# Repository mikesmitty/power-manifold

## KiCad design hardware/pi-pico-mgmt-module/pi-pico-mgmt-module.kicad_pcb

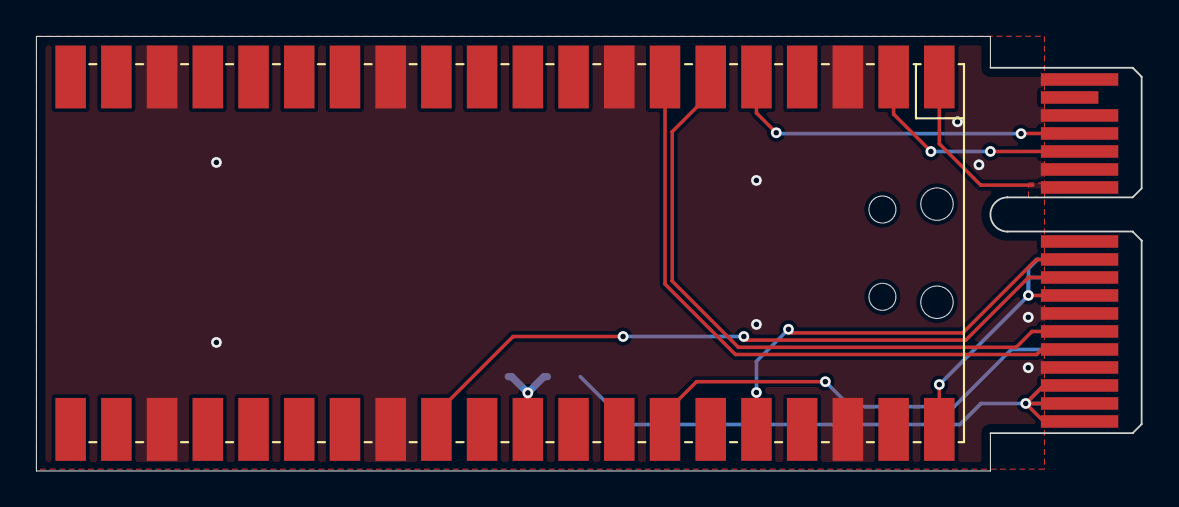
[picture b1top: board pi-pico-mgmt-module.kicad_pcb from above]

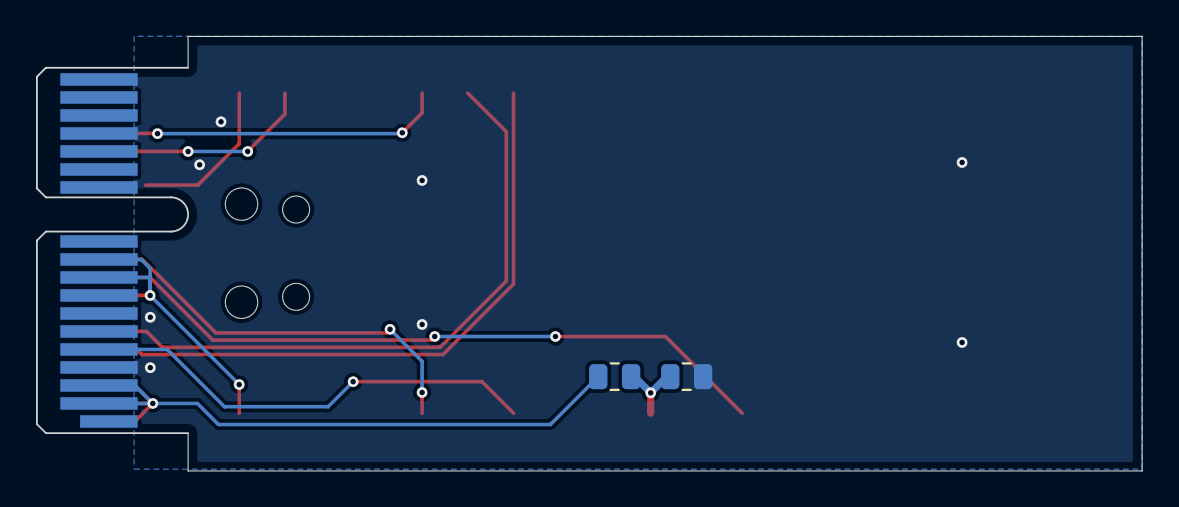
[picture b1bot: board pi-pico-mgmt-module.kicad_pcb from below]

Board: 2 copper layers, 61.4 x 24.1 mm, 4 parts (2 on the bottom side), 12 nets.

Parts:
J1: Bus_PCI_Express_x1; BUS_PCIexpress_x1
R1: 22K; R_0805_2012Metric
R2: 2K; R_0805_2012Metric
U1: W5500-EVB-Pico; RPi_Pico_W5500_SMD_NO_HOLES

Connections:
+5V: J1.A9 (+3.3V), J1.A10 (+3.3V), J1.B8 (+3.3V), U1.40 (VBUS)
GND: J1.A4 (GND), J1.A12 (GND), J1.A15 (GND), J1.A18 (GND), J1.B4 (GND), J1.B7 (GND), J1.B13 (GND), J1.B16 (GND), J1.B18 (GND), R2.2, U1.3 (GND), U1.8 (GND), U1.13 (GND), U1.18 (GND), U1.23 (GND), U1.28 (GND), U1.38 (GND)
I2C_A0: J1.B5 (SMCLK), U1.7 (GPIO5)
I2C_A1: J1.B6 (SMDAT), U1.6 (GPIO4)
I2C_A2: J1.B15 (PETn0), U1.5 (GPIO3)
I2C_RESET: J1.B9 (JTAG1), U1.29 (GPIO22)
unnamed: R1.2, R2.1, U1.31 (GPIO26_ADC0)
OVERLOAD: J1.A5 (JTAG2), U1.34 (GPIO28_ADC2)
SCL: J1.B14 (PETp0), U1.2 (GPIO1)
SDA: J1.B12 (RSVD), U1.1 (GPIO0)
VDD: J1.B10 (3.3Vaux), U1.36 (3V3)
VIN: J1.A2 (+12V), J1.A3 (+12V), J1.B1 (+12V), J1.B2 (+12V), J1.B3 (+12V), R1.1

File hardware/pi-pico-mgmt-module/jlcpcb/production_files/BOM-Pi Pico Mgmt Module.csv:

Comment,Designator,Footprint,LCSC
22K,R1,R_0805_2012Metric,C17560
2K,R2,R_0805_2012Metric,C17604

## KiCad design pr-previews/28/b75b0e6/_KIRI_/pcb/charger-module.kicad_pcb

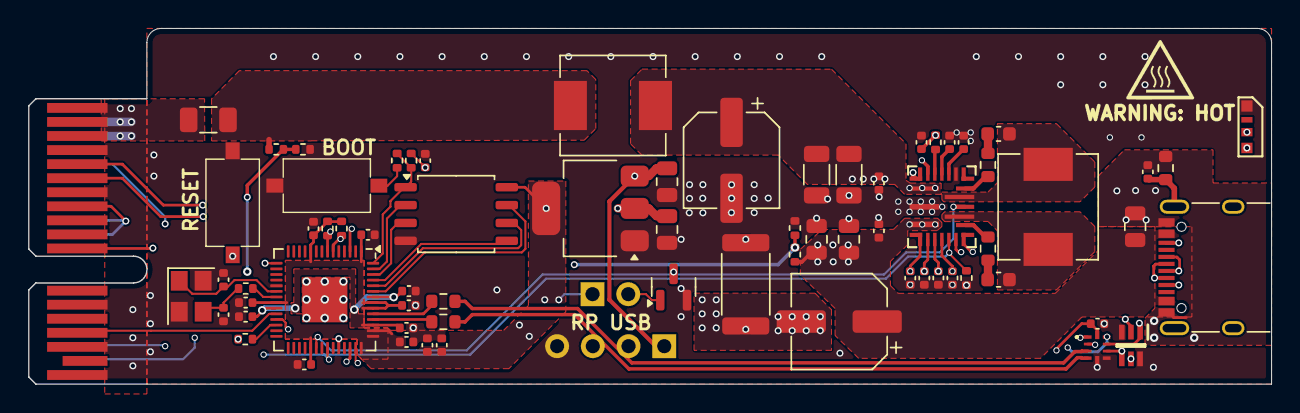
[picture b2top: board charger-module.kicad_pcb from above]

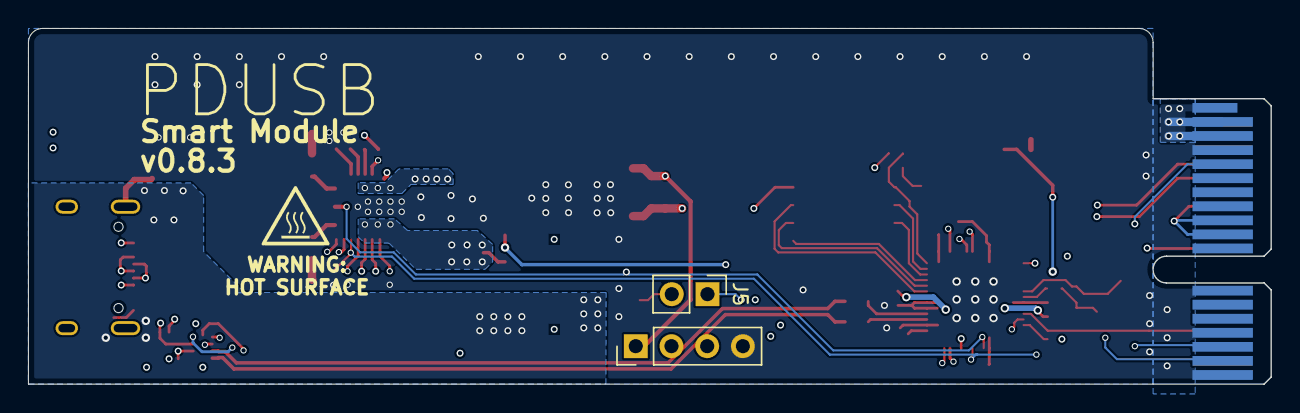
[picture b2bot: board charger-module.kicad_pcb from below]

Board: 4 copper layers, 88.4 x 25.3 mm, 72 parts (2 on the bottom side), 53 nets.

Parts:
C1, C4, C21, C24, C28: 10uF; C_0805_2012Metric
C2, C3: 39pF; C_0402_1005Metric
C5, C6, C9, C14, C15, C17, C20, C22, C25, C26, C27, C30, C35: 100nF; C_0402_1005Metric
C7, C10, C16: 2.2uF; C_0402_1005Metric
C8, C31, C32, C33, C34, C36: 470pF; C_0402_1005Metric
C11, C29: 100uF; CP_Elec_6.3x7.7
C12, C13: 4.7uF; C_1206_3216Metric
C18, C23: 220nF; C_0603_1608Metric
C19: 4.7nF; C_0402_1005Metric
D1: SZESD1L001W1T2G; SOT65P210X110-6N
D2: STATUS_LED; LED_Neopixel_Side_Light_SK6812
F1: 5A; Fuse_1206_3216Metric
J2: Bus_PCI_Express_x1; BUS_PCIexpress_x1
J3: RP_USB; PinHeader_1x04_P2.54mm_Vertical
J4: USB_C_Receptacle_USB2.0_14P; USB_C_Receptacle_XKB_U262-16XN-4BVC11
J5: USB_SW; PinHeader_1x02_P2.54mm_Vertical
L1, L2: 4.7uH; L_Sunlord_MWSA0603S
Q1: 2N7002; SOT-23
R1, R3, R4: 1K; R_0402_1005Metric
R2, R5, R11, R13: 10K; R_0402_1005Metric
R6: R010; R_2512_6332Metric
R7: 10R; R_0603_1608Metric
R8: 4.7K; R_0402_1005Metric
R9, R10: 27R; R_0603_1608Metric
R12: 0R; R_0603_1608Metric
R14, R16: 22K; R_0402_1005Metric
R15: 2K; R_0402_1005Metric
R17: 3.3K; R_0402_1005Metric
R18: 100K; R_0603_1608Metric
SW1, SW2: RESET; XKB_TS-1101_SWITCH
U1: AMS1117-3.3; SOT-223-3_TabPin2
U2: W25Q32JVSSIQ; SOIC-8_5.23x5.23mm_P1.27mm
U3: RP2040; QFN-56-1EP_7x7mm_P0.4mm_EP3.2x3.2mm
U4: MPQ4242; MPQ4242_QNF-22_4mmx5mm
U5: TS3USB3000RSER
Y1: X322512MSB4SI; Crystal_SMD_3225-4Pin_3.2x2.5mm

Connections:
+1V1: C6.1, C9.1, C10.1, U3.23 (DVDD), U3.45 (VREG_VOUT), U3.50 (DVDD)
+3.3V: C4.1, C5.1, C15.1, C16.1, C17.1, C20.1, C22.1, C25.1, C27.1, C30.1, C36.1, J5.1, R2.1, R11.1, R13.1, U1.2 (VO), U2.8 (VCC), U3.1 (IOVDD), U3.10 (IOVDD), U3.22 (IOVDD), U3.33 (IOVDD), U3.42 (IOVDD), U3.43 (ADC_AVDD), U3.44 (VREG_IN), U3.48 (USB_VDD), U3.49 (IOVDD), U5.10 (VCC)
+5V: C1.1, D2.2 (VDD), J2.A9 (+3.3V), J2.A10 (+3.3V), J2.B8 (+3.3V), J3.1, U1.3 (VI)
/EMI_VIN: C11.1, C12.1, C13.1, C14.1, L1.2, U4.1 (VIN)
/INDUCTOR: C18.2, L2.1, U4.14 (SW1)
/OUTDUCTOR: C23.1, L2.2, U4.12 (SW2)
/QSPI_SCLK: U2.6 (CLK), U3.52 (QSPI_SCLK)
/QSPI_SD0: U2.5 (DI(IO0)), U3.53 (QSPI_SD0)
/QSPI_SD1: U2.2 (DO(IO1)), U3.55 (QSPI_SD1)
/QSPI_SD2: U2.3 (IO2), U3.54 (QSPI_SD2)
/QSPI_SD3: U2.7 (IO3), U3.51 (QSPI_SD3)
/QSPI_SS: R1.1, R2.2, U2.1 (~CS), U3.56 (QSPI_SS)
/RUN: R4.2, U3.26 (RUN)
/SWCLK: J2.B15 (PETn0), U3.24 (SWCLK)
/SWD: J2.A5 (JTAG2), U3.25 (SWD)
/VIN_PREFUSE: F1.2, J2.A1 (~PRSNT1), J2.A2 (+12V), J2.A3 (+12V), J2.B1 (+12V), J2.B2 (+12V), J2.B3 (+12V)
/XIN: C2.1, U3.20 (XIN), Y1.1
/XOUT: R3.1, U3.21 (XOUT)
ALERT: J2.A17 (PERn0), U3.15 (GPIO12)
CC1: C33.1, D1.2 (C2), J4.A5 (CC1), U4.7 (CC1)
CC2: C34.1, D1.5 (C4), J4.B5 (CC2), U4.4 (CC2)
D+: D1.1 (C1), J4.A6 (D+), J4.B6 (D+), U5.8 (D+)
D-: D1.4 (C3), J4.A7 (D-), J4.B7 (D-), U5.7 (D-)
ENABLE: Q1.3 (D), U3.34 (GPIO22), U4.13 (EN)
GND: C1.2, C2.2, C3.2, C4.2, C5.2, C6.2, C7.2, C8.2, C9.2, C10.2, C11.2, C12.2, C13.2, C14.2, C15.2, C16.2, C17.2, C19.1, C20.2, C21.2, C22.2, C24.2, C25.2, C26.2, C27.2, C30.2, C31.2, C32.2, C33.2, C34.2, C36.2, D1.3 (A/3+4), D1.6 (A/1+2), D2.4 (GND), J2.A4 (GND), J2.A12 (GND), J2.A15 (GND), J2.A18 (GND), J2.B4 (GND), J2.B7 (GND), J2.B13 (GND), J2.B16 (GND), J2.B18 (GND), J3.4, Q1.2 (S), R5.2, R6.1, R15.2, R17.2, SW1.1, SW2.1, U1.1 (GND), U2.4 (GND), U3.19 (TESTEN), U3.57 (GND), U4.2 (PGND), U4.17 (AGND), U4.21 (ISENS-), U5.5 (GND), U5.6 (~OE), Y1.2, Y1.4
GNDUSB: C28.1, C29.2, C35.2, J4.A1 (GND), J4.A12 (GND), J4.B1 (GND), J4.B12 (GND), R6.2, R18.2, U4.22 (ISENS+)
IMON: C19.2, R8.1, U3.38 (GPIO26_ADC0)
LED_DIN: D2.1 (DIN), U3.3 (GPIO1)
MPQ_D+: C32.1, U4.5 (DP), U5.1 (USB+)
MPQ_D-: C31.1, U4.6 (DM), U5.2 (USB-)
unnamed: C3.1, R3.2, Y1.3
unnamed: C18.1, R7.2
unnamed: C23.2, R12.1
unnamed: C35.1, J4.S1 (SHIELD), R18.1
unnamed: J5.2, Q1.1 (G), U5.9 (SEL)
unnamed: R1.2, SW1.2
unnamed: R4.1, SW2.2
unnamed: R10.2, U3.46 (USB_DM)
unnamed: R9.2, U3.47 (USB_DP)
unnamed: R7.1, U4.15 (BST1)
unnamed: R12.2, U4.11 (BST2)
unnamed: R8.2, U4.20 (GPIO1)
unnamed: C8.1, U4.19 (ICOMP)
OVERLOAD: J2.A16 (PERp0), R5.1, U3.36 (GPIO24), U4.8 (GPIO2)
RP_D+: J3.2, R9.1, U5.3 (MHL+)
RP_D-: J3.3, R10.1, U5.4 (MHL-)
SCL: J2.B5 (SMCLK), R13.2, U3.7 (GPIO5), U4.10 (SCL)
SDA: J2.B6 (SMDAT), R11.2, U3.6 (GPIO4), U4.9 (SDA)
VBUS: C21.1, C24.1, C26.1, C28.2, C29.1, J4.A4 (VBUS), J4.A9 (VBUS), J4.B4 (VBUS), J4.B9 (VBUS), R16.1, U4.3 (OUT)
VCC: C7.1, U4.18 (VCC)
VIN: F1.1, L1.1, R14.1
VIN_DIVIDER: R14.2, R15.1, U3.40 (GPIO28_ADC2)
VOUT_DIVIDER: R16.2, R17.1, U3.41 (GPIO29_ADC3)

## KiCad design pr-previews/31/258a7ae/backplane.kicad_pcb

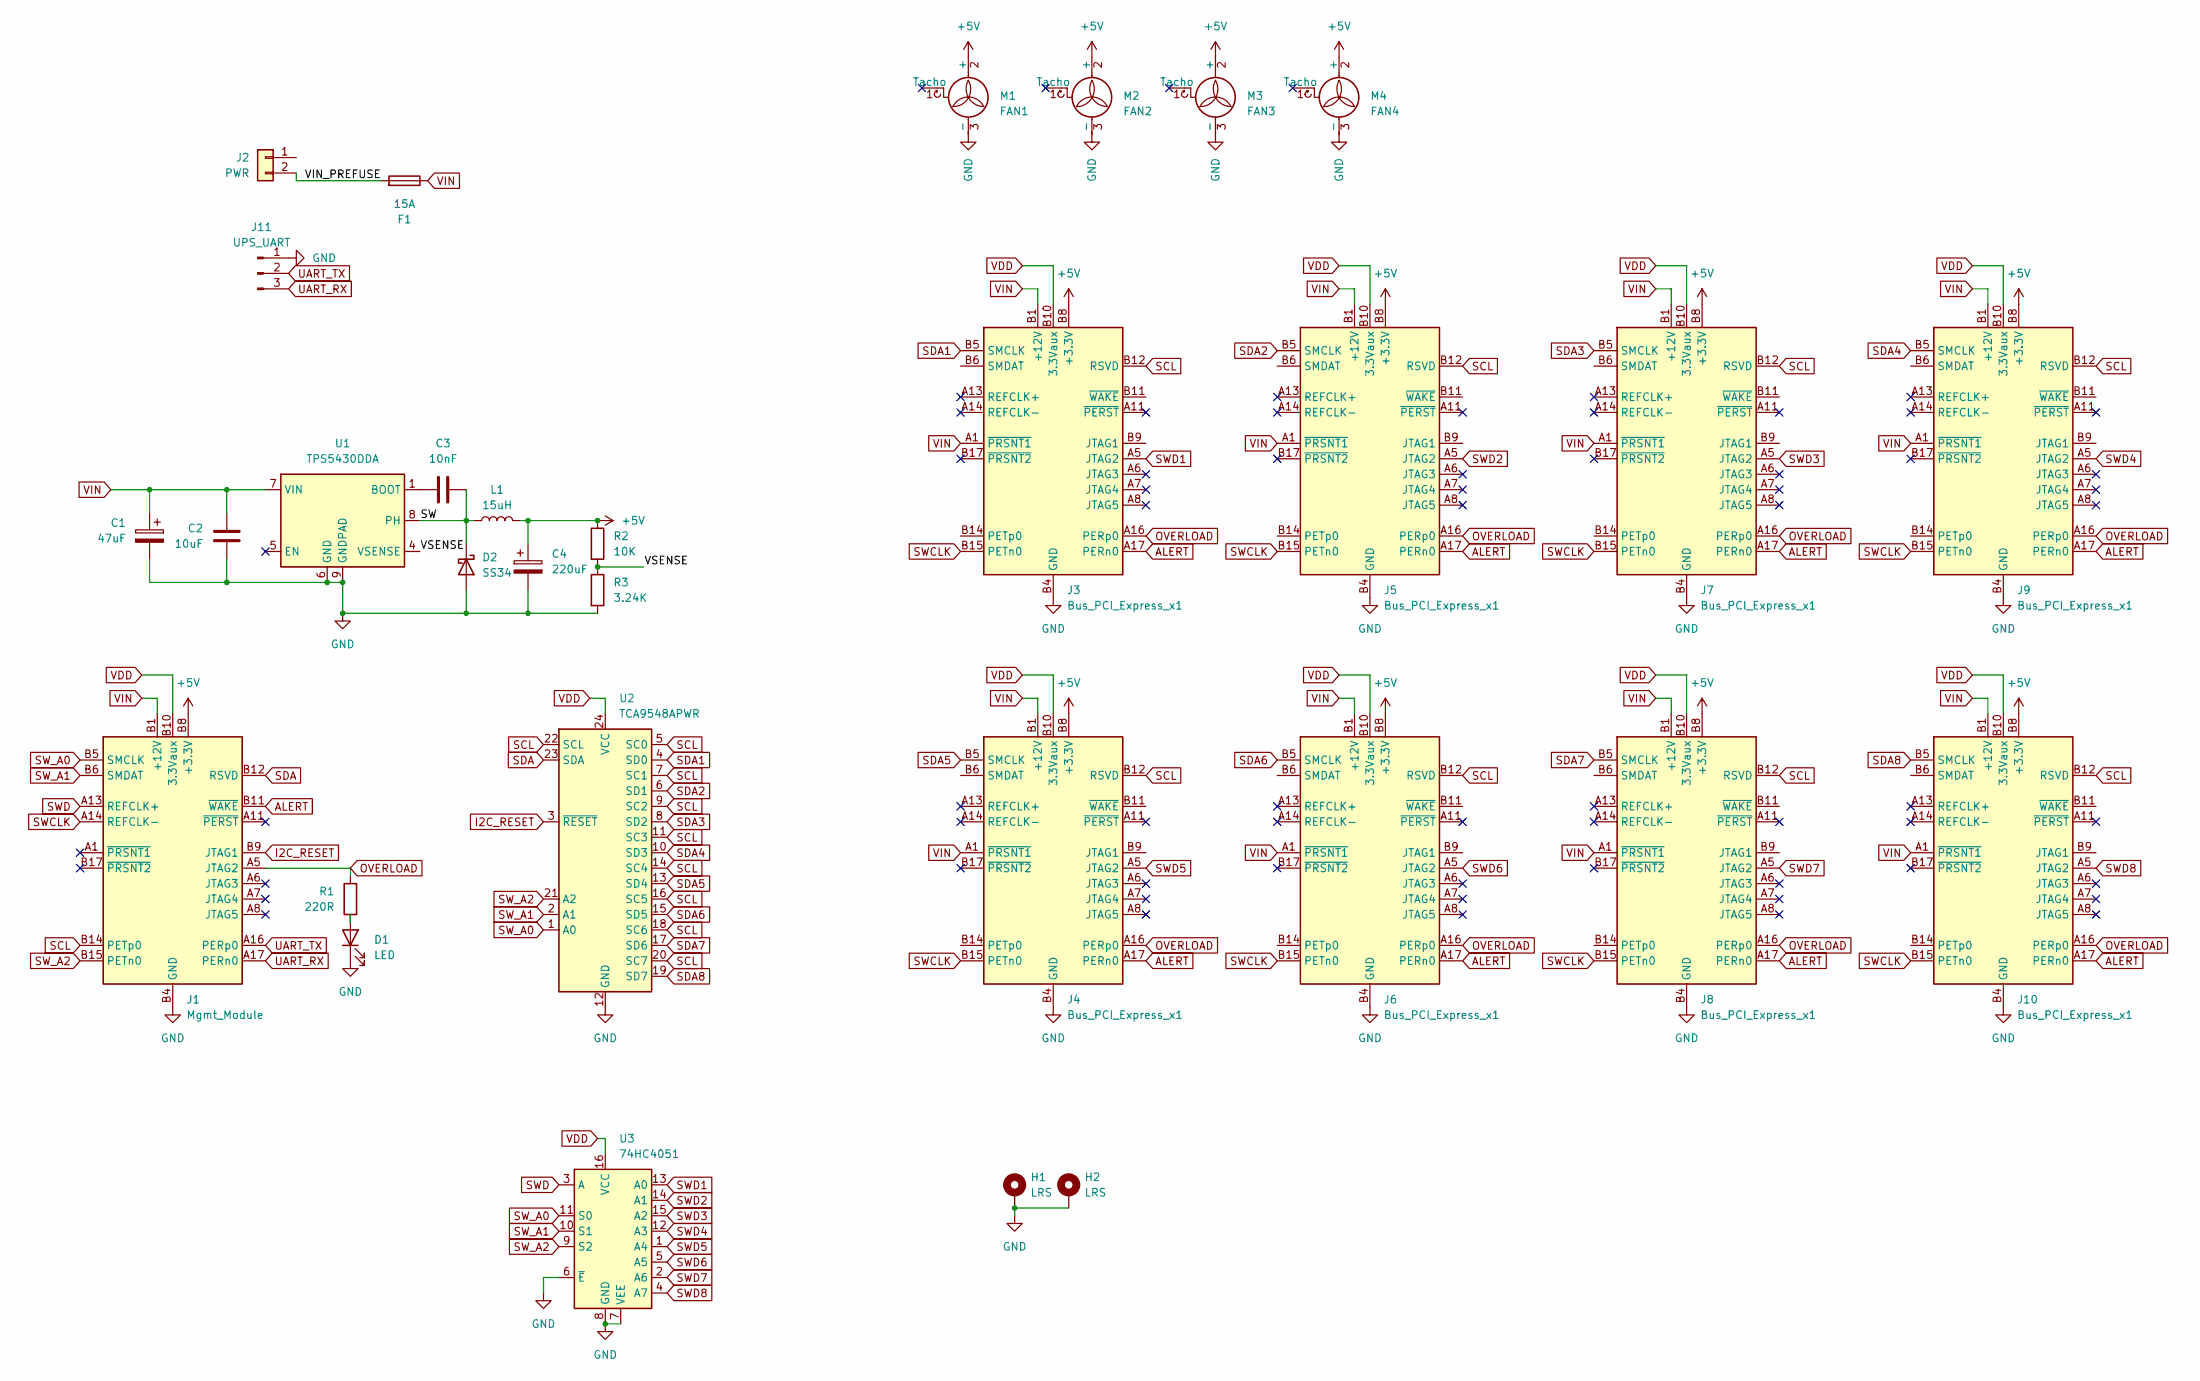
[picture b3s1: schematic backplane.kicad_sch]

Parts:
C1: 47uF; CP_Elec_6.3x7.7; LCSC C72523
C2: 10uF; C_0805_2012Metric; LCSC C440198
C3: 10nF; C_0603_1608Metric; LCSC C1589
C4: 220uF; CP_Elec_6.3x5.4_Nichicon; LCSC C72494
D1: LED; LED_0603_1608Metric; LCSC C2286
D2: SS34; D_SMA; LCSC C8678
F1: 15A; Fuseholder_Blade_Mini_Keystone_3568
H1, H2: LRS; MountingHole_4.3mm_M4_DIN965_Pad
J1: Mgmt_Module; AMPHENOL_PCI_E_10018783-10210TLF
J2: PWR; AMASS_XT30PW-M_1x02_P2.50mm_Horizontal; LCSC C431092
J3, J4, J5, J6, J7, J8, J9, J10: Bus_PCI_Express_x1; AMPHENOL_PCI_E_10018783-10210TLF
J11: UPS_UART; JST_XH_S3B-XH-A-1_1x03_P2.50mm_Horizontal
L1: 15uH; L_Sunlord_MWSA0603S; LCSC C408452
M1: FAN1; FanPinHeader_1x03_P2.54mm_Vertical
M2: FAN2; FanPinHeader_1x03_P2.54mm_Vertical
M3: FAN3; FanPinHeader_1x03_P2.54mm_Vertical
M4: FAN4; FanPinHeader_1x03_P2.54mm_Vertical
R1: 220R; R_0603_1608Metric; LCSC C22962
R2: 10K; R_0603_1608Metric; LCSC C25804
R3: 3.24K; R_0603_1608Metric; LCSC C22994
U1: TPS5430DDA; TI_SO-PowerPAD-8_ThermalVias; LCSC C9864
U2: TCA9548APWR; TSSOP-24_4.4x7.8mm_P0.65mm; LCSC C130026
U3: 74HC4051; TSSOP-16_4.4x5mm_P0.65mm; LCSC C5645

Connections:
+5V: C4.1, J1.A9 (+3.3V), J1.A10 (+3.3V), J1.B8 (+3.3V), J3.A9 (+3.3V), J3.A10 (+3.3V), J3.B8 (+3.3V), J4.A9 (+3.3V), J4.A10 (+3.3V), J4.B8 (+3.3V), J5.A9 (+3.3V), J5.A10 (+3.3V), J5.B8 (+3.3V), J6.A9 (+3.3V), J6.A10 (+3.3V), J6.B8 (+3.3V), J7.A9 (+3.3V), J7.A10 (+3.3V), J7.B8 (+3.3V), J8.A9 (+3.3V), J8.A10 (+3.3V), J8.B8 (+3.3V), J9.A9 (+3.3V), J9.A10 (+3.3V), J9.B8 (+3.3V), J10.A9 (+3.3V), J10.A10 (+3.3V), J10.B8 (+3.3V), L1.2, M1.2 (+), M2.2 (+), M3.2 (+), M4.2 (+), R2.1
/SW: C3.2, D2.1 (K), L1.1, U1.8 (PH)
/VIN_PREFUSE: F1.2, J2.2
/VSENSE: R2.2, R3.1, U1.4 (VSENSE)
ALERT: J1.B11 (~WAKE), J3.A17 (PERn0), J4.A17 (PERn0), J5.A17 (PERn0), J6.A17 (PERn0), J7.A17 (PERn0), J8.A17 (PERn0), J9.A17 (PERn0), J10.A17 (PERn0)
GND: C1.2, C2.2, C4.2, D1.1 (K), D2.2 (A), H1.1, H2.1, J1.A4 (GND), J1.A12 (GND), J1.A15 (GND), J1.A18 (GND), J1.B4 (GND), J1.B7 (GND), J1.B13 (GND), J1.B16 (GND), J1.B18 (GND), J3.A4 (GND), J3.A12 (GND), J3.A15 (GND), J3.A18 (GND), J3.B4 (GND), J3.B7 (GND), J3.B13 (GND), J3.B16 (GND), J3.B18 (GND), J4.A4 (GND), J4.A12 (GND), J4.A15 (GND), J4.A18 (GND), J4.B4 (GND), J4.B7 (GND), J4.B13 (GND), J4.B16 (GND), J4.B18 (GND), J5.A4 (GND), J5.A12 (GND), J5.A15 (GND), J5.A18 (GND), J5.B4 (GND), J5.B7 (GND), J5.B13 (GND), J5.B16 (GND), J5.B18 (GND), J6.A4 (GND), J6.A12 (GND), J6.A15 (GND), J6.A18 (GND), J6.B4 (GND), J6.B7 (GND), J6.B13 (GND), J6.B16 (GND), J6.B18 (GND), J7.A4 (GND), J7.A12 (GND), J7.A15 (GND), J7.A18 (GND), J7.B4 (GND), J7.B7 (GND), J7.B13 (GND), J7.B16 (GND), J7.B18 (GND), J8.A4 (GND), J8.A12 (GND), J8.A15 (GND), J8.A18 (GND), J8.B4 (GND), J8.B7 (GND), J8.B13 (GND), J8.B16 (GND), J8.B18 (GND), J9.A4 (GND), J9.A12 (GND), J9.A15 (GND), J9.A18 (GND), J9.B4 (GND), J9.B7 (GND), J9.B13 (GND), J9.B16 (GND), J9.B18 (GND), J10.A4 (GND), J10.A12 (GND), J10.A15 (GND), J10.A18 (GND), J10.B4 (GND), J10.B7 (GND), J10.B13 (GND), J10.B16 (GND), J10.B18 (GND), J11.1, M1.3 (-), M2.3 (-), M3.3 (-), M4.3 (-), R3.2, U1.6 (GND), U1.9 (GNDPAD), U2.12 (GND), U3.6 (~E), U3.7 (VEE), U3.8 (GND)
I2C_RESET: J1.B9 (JTAG1), U2.3 (~RESET)
unnamed: D1.2 (A), R1.2
unnamed: C3.1, U1.1 (BOOT)
OVERLOAD: J1.A5 (JTAG2), J3.A16 (PERp0), J4.A16 (PERp0), J5.A16 (PERp0), J6.A16 (PERp0), J7.A16 (PERp0), J8.A16 (PERp0), J9.A16 (PERp0), J10.A16 (PERp0), R1.1
SCL: J1.B14 (PETp0), J3.B12 (RSVD), J4.B12 (RSVD), J5.B12 (RSVD), J6.B12 (RSVD), J7.B12 (RSVD), J8.B12 (RSVD), J9.B12 (RSVD), J10.B12 (RSVD), U2.5 (SC0), U2.7 (SC1), U2.9 (SC2), U2.11 (SC3), U2.14 (SC4), U2.16 (SC5), U2.18 (SC6), U2.20 (SC7), U2.22 (SCL)
SDA: J1.B12 (RSVD), U2.23 (SDA)
SDA1: J3.B5 (SMCLK), U2.4 (SD0)
SDA2: J5.B5 (SMCLK), U2.6 (SD1)
SDA3: J7.B5 (SMCLK), U2.8 (SD2)
SDA4: J9.B5 (SMCLK), U2.10 (SD3)
SDA5: J4.B5 (SMCLK), U2.13 (SD4)
SDA6: J6.B5 (SMCLK), U2.15 (SD5)
SDA7: J8.B5 (SMCLK), U2.17 (SD6)
SDA8: J10.B5 (SMCLK), U2.19 (SD7)
SWCLK: J1.A14 (REFCLK-), J3.B15 (PETn0), J4.B15 (PETn0), J5.B15 (PETn0), J6.B15 (PETn0), J7.B15 (PETn0), J8.B15 (PETn0), J9.B15 (PETn0), J10.B15 (PETn0)
SWD: J1.A13 (REFCLK+), U3.3 (A)
SWD1: J3.A5 (JTAG2), U3.13 (A0)
SWD2: J5.A5 (JTAG2), U3.14 (A1)
SWD3: J7.A5 (JTAG2), U3.15 (A2)
SWD4: J9.A5 (JTAG2), U3.12 (A3)
SWD5: J4.A5 (JTAG2), U3.1 (A4)
SWD6: J6.A5 (JTAG2), U3.5 (A5)
SWD7: J8.A5 (JTAG2), U3.2 (A6)
SWD8: J10.A5 (JTAG2), U3.4 (A7)
SW_A0: J1.B5 (SMCLK), U2.1 (A0), U3.11 (S0)
SW_A1: J1.B6 (SMDAT), U2.2 (A1), U3.10 (S1)
SW_A2: J1.B15 (PETn0), U2.21 (A2), U3.9 (S2)
UART_RX: J1.A17 (PERn0), J11.3
UART_TX: J1.A16 (PERp0), J11.2
VDD: J1.B10 (3.3Vaux), J3.B10 (3.3Vaux), J4.B10 (3.3Vaux), J5.B10 (3.3Vaux), J6.B10 (3.3Vaux), J7.B10 (3.3Vaux), J8.B10 (3.3Vaux), J9.B10 (3.3Vaux), J10.B10 (3.3Vaux), U2.24 (VCC), U3.16 (VCC)
VIN: C1.1, C2.1, F1.1, J1.A2 (+12V), J1.A3 (+12V), J1.B1 (+12V), J1.B2 (+12V), J1.B3 (+12V), J3.A1 (~PRSNT1), J3.A2 (+12V), J3.A3 (+12V), J3.B1 (+12V), J3.B2 (+12V), J3.B3 (+12V), J4.A1 (~PRSNT1), J4.A2 (+12V), J4.A3 (+12V), J4.B1 (+12V), J4.B2 (+12V), J4.B3 (+12V), J5.A1 (~PRSNT1), J5.A2 (+12V), J5.A3 (+12V), J5.B1 (+12V), J5.B2 (+12V), J5.B3 (+12V), J6.A1 (~PRSNT1), J6.A2 (+12V), J6.A3 (+12V), J6.B1 (+12V), J6.B2 (+12V), J6.B3 (+12V), J7.A1 (~PRSNT1), J7.A2 (+12V), J7.A3 (+12V), J7.B1 (+12V), J7.B2 (+12V), J7.B3 (+12V), J8.A1 (~PRSNT1), J8.A2 (+12V), J8.A3 (+12V), J8.B1 (+12V), J8.B2 (+12V), J8.B3 (+12V), J9.A1 (~PRSNT1), J9.A2 (+12V), J9.A3 (+12V), J9.B1 (+12V), J9.B2 (+12V), J9.B3 (+12V), J10.A1 (~PRSNT1), J10.A2 (+12V), J10.A3 (+12V), J10.B1 (+12V), J10.B2 (+12V), J10.B3 (+12V), U1.7 (VIN)

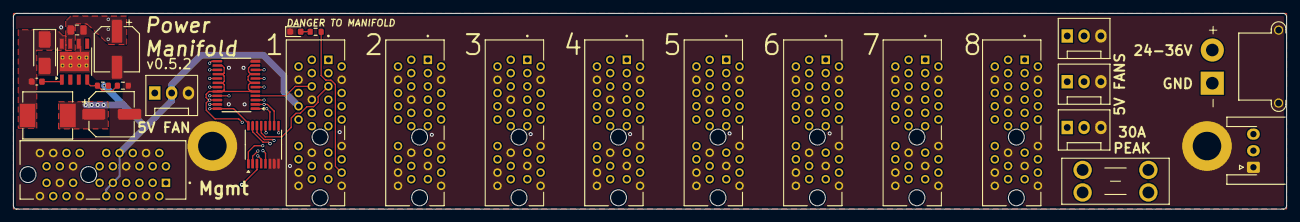
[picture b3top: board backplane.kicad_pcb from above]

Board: 4 copper layers, 192.0 x 29.5 mm, 31 parts (0 on the bottom side), 37 nets.

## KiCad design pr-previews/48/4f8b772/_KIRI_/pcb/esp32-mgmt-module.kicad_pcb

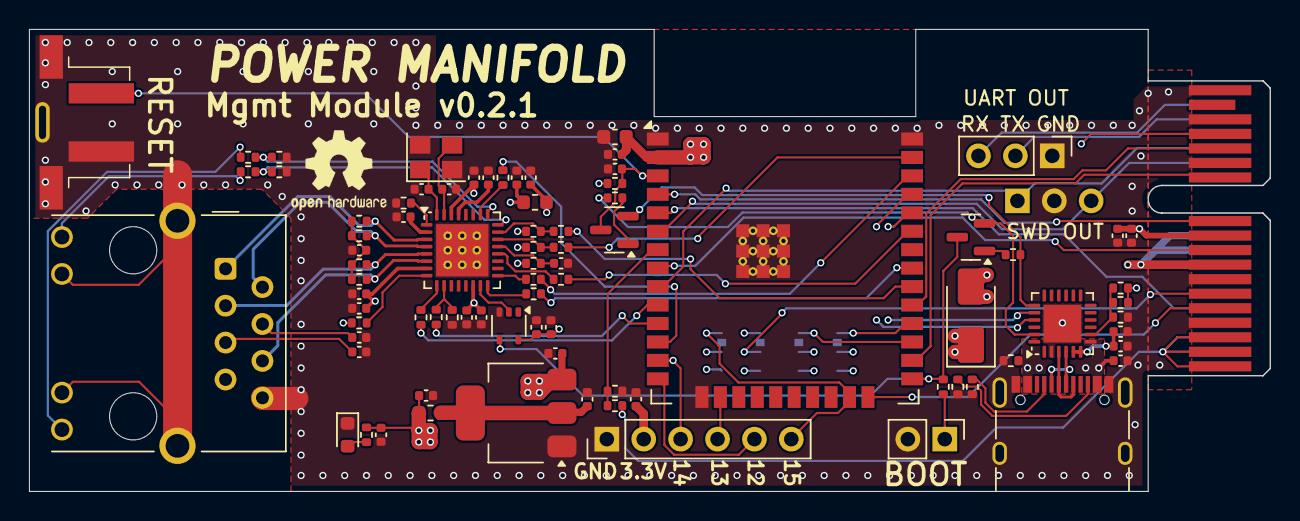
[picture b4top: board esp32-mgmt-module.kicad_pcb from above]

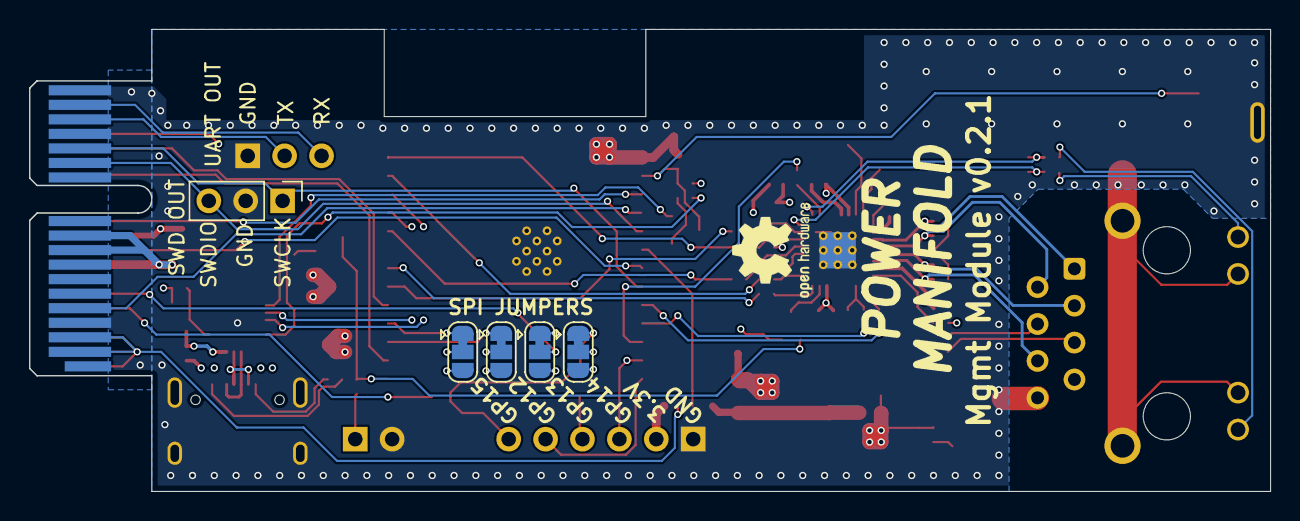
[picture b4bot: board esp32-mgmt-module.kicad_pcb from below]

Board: 4 copper layers, 85.4 x 31.8 mm, 89 parts (5 on the bottom side), 77 nets.

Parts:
C1, C6: 10pF; C_0402_1005Metric
C2, C3, C5, C7, C8, C12, C14, C15, C18, C20, C21, C22, C26, C30, C32, C34: 100nF; C_0402_1005Metric
C4, C9, C10, C11, C16, C17, C33: 1uF; C_0402_1005Metric
C13, C19, C24, C35: 10uF; C_0402_1005Metric
C31: 22uF; C_0603_1608Metric
D1: SS54; D_SMA
D4: RED; LED_0603_1608Metric
J1: Bus_PCI_Express_x1; BUS_PCIexpress_x1
J2: BOOT; PinHeader_1x02_P2.54mm_Vertical
J3: RJ45_Hanrun_HR913550A_Horizontal; RJ45_Hanrun_HR911105A_Horizontal
J4: GPIO; PinHeader_1x06_P2.54mm_Vertical
J5: SWD; PinHeader_1x03_P2.54mm_Vertical
J6: USB_C; USB_C_Receptacle_XKB_U262-16XN-4BVC11
J7: UART; PinHeader_1x03_P2.54mm_Vertical
JP1: TXD; SolderJumper-3_P1.3mm_Bridged12_RoundedPad1.0x1.5mm
JP2: RXD; SolderJumper-3_P1.3mm_Bridged12_RoundedPad1.0x1.5mm
JP3: SW_A1; SolderJumper-3_P1.3mm_Bridged12_RoundedPad1.0x1.5mm
JP4: SW_A2; SolderJumper-3_P1.3mm_Bridged12_RoundedPad1.0x1.5mm
L1, L2: 600R; L_0603_1608Metric
Q1, Q2: MMBT3904; SOT-23
R1, R2, R26, R28, R29, R30: 4.7K; R_0402_1005Metric
R3: 39K; R_0402_1005Metric
R4: 1K; R_0402_1005Metric
R5, R6, R7, R8, R9, R10, R12, R13: 22R; R_0402_1005Metric
R11, R16, R17, R18, R19, R20, R21: 10K; R_0402_1005Metric
R14: 100K; R_0402_1005Metric
R15: 2.49K 1%; R_0402_1005Metric
R22, R23, R24, R25: 49.9R; R_0402_1005Metric
R27: 220R; R_0402_1005Metric
R31, R32, R33: 47K; R_0402_1005Metric
R34, R35: 5.1K; R_0402_1005Metric
SW1: RESET; Yuandi_TS-1037-Ax
U1: RTL8201F-VB-CG; QFN-32-1EP_5x5mm_P0.5mm_EP3.6x3.6mm_ThermalVias
U2: 74LVC1G14; SOT-353_SC-70-5
U3: AMS1117-3.3; SOT-223-3_TabPin2
U4: ESP32-WROOM-32E
U5: CH9102F; QFN-24-1EP_4x4mm_P0.5mm_EP2.6x2.6mm
Y1: 25MHz; Crystal_SMD_3225-4Pin_3.2x2.5mm

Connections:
+3.3V: C8.1, C9.1, C10.1, C12.1, C14.1, C15.1, C16.1, C22.1, C24.1, C30.2, C31.2, C35.1, J1.B10 (3.3Vaux), J4.2, L1.1, L2.2, R2.1, R16.2, R17.2, R18.2, R19.2, R26.1, U1.14 (DVDD33), U2.5 (VCC), U4.2 (VDD)
+3.3VA: C4.1, C7.1, C17.1, C21.1, L1.2, U1.7 (AVDD33), U1.30 (AVDD33)
+5V: C34.1, D1.2 (A), J1.A9 (+3.3V), J1.A10 (+3.3V), J1.B8 (+3.3V), J6.A4 (VBUS), J6.A9 (VBUS), J6.B4 (VBUS), J6.B9 (VBUS), R14.1, R31.1, R33.1, U5.7 (VDD5)
/3.45V: C32.1, C33.1, U5.5 (VIO), U5.6 (V3)
/CKXTAL1: C6.1, U1.31 (CKXTAL1), Y1.3
/CKXTAL2: C1.1, U1.32 (CKXTAL2), Y1.1
/D+: J6.A6 (D+), J6.B6 (D+), U5.3 (D+)
/D-: J6.A7 (D-), J6.B7 (D-), U5.4 (D-)
/DTR: Q1.2 (E), R21.1, U5.23 (~DTR)
/EMAC_RXD0: R8.1, U4.10 (IO25)
/EMAC_RXD1: R9.1, U4.11 (IO26)
/EMAC_RX_DV: R10.1, U4.12 (IO27)
/EMAC_TXD0: R5.1, U4.31 (IO19)
/EMAC_TXD1: R6.1, U4.36 (IO22)
/EMAC_TX_EN: R7.1, U4.33 (IO21)
/ETH_MDC: R12.2, U4.37 (IO23)
/ETH_MDIO: R13.2, U4.30 (IO18)
/GPIO12: J4.5, U4.14 (IO12)
/GPIO13: J4.4, U4.16 (IO13)
/GPIO14: J4.3, JP3.1 (A), U4.13 (IO14)
/GPIO15: J4.6, JP4.1 (A), U4.23 (IO15)
/LED_ACT: R28.1, R30.1, U1.24 (LED0)
/LED_LINK: R27.2, R29.2, U1.25 (LED1)
/OVERLOAD: J1.A5 (JTAG2), U4.5 (SENSOR_VN)
/REF_CLK_ETH: U1.15 (TXC), U2.2
/REF_CLK_MCU: Q1.3 (C), R11.2, U2.4, U4.25 (IO0)
/RTS: Q2.2 (E), R20.1, U5.19 (~RTS)
/RXD0: JP2.3 (B), U4.34 (RXD0/IO3), U5.20 (RXD)
/RXD2: JP2.1 (A), JP4.3 (B), U4.27 (IO16)
/RXD_OUT: J1.A17 (PERn0), J7.3, JP2.2 (C)
/RX_D+: J3.3 (RD+), R24.1, U1.5 (MDI+[1])
/RX_D-: J3.6 (RD-), R25.1, U1.6 (MDI-[1])
/SCL: J1.B14 (PETp0), U4.29 (IO5)
/SDA: J1.B12 (RSVD), U4.26 (IO4)
/SWCLK: J1.A14 (REFCLK-), J5.1, U4.9 (IO33)
/SWDIO: J1.A13 (REFCLK+), J5.3, U4.6 (IO34)
/SW_A0: J1.B5 (SMCLK), U4.24 (IO2)
/SW_A1: J1.B6 (SMDAT), JP3.2 (C)
/SW_A2: J1.B15 (PETn0), JP4.2 (C)
/TXD0: JP1.3 (B), U4.35 (TXD0/IO1), U5.21 (TXD)
/TXD2: JP1.1 (A), JP3.3 (B), U4.28 (IO17)
/TXD_OUT: J1.A16 (PERp0), J7.2, JP1.2 (C)
/TX_D+: J3.1 (TD+), R22.1, U1.3 (MDI+[0])
/TX_D-: J3.2 (TD-), R23.1, U1.4 (MDI-[0])
/VIN: J1.A2 (+12V), J1.A3 (+12V), J1.B1 (+12V), J1.B2 (+12V), J1.B3 (+12V), R3.1
/VIN_ADC1: R3.2, R4.1, U4.7 (IO35)
/~ALERT: J1.B11 (~WAKE), U4.4 (SENSOR_VP)
/~I2C_RESET: J1.B9 (JTAG1), U4.8 (IO32)
/~RESET: C11.1, Q2.3 (C), R16.1, SW1.2, U4.3 (EN)
GND: C1.2, C2.1, C3.2, C4.2, C5.1, C6.2, C7.2, C8.2, C9.2, C10.2, C11.2, C12.2, C13.2, C14.2, C15.2, C16.2, C17.2, C18.2, C19.2, C20.2, C21.2, C22.2, C24.2, C26.2, C30.1, C31.1, C32.2, C33.2, C34.2, C35.2, D4.1 (K), J1.A4 (GND), J1.A12 (GND), J1.A15 (GND), J1.A18 (GND), J1.B4 (GND), J1.B7 (GND), J1.B13 (GND), J1.B16 (GND), J1.B18 (GND), J2.2, J3.8, J3.10, J3.11, J3.SH, J4.1, J5.2, J6.A1 (GND), J6.A12 (GND), J6.B1 (GND), J6.B12 (GND), J6.S1 (SHIELD), J7.1, R1.1, R4.2, R14.2, R15.1, R29.1, R30.2, R32.2, R34.1, R35.1, SW1.1, U1.33 (GND), U2.3 (GND), U3.1 (GND), U4.1 (GND), U4.15 (GND), U4.38 (GND), U4.39 (GND), U5.2 (GND), U5.25 (GND), Y1.2, Y1.4
unnamed: C26.1, R22.2, R23.2, R24.2, R25.2
unnamed: C13.1, D1.1 (K), U3.3 (VI)
unnamed: D4.2 (A), R26.2
unnamed: J2.1, R11.1
unnamed: J3.9, R28.2
unnamed: J3.12, R27.1
unnamed: C20.1, J3.5 (RCT)
unnamed: C18.1, J3.4 (TCT)
unnamed: J6.A5 (CC1), R34.2
unnamed: J6.B5 (CC2), R35.2
unnamed: Q1.1 (B), R20.2
unnamed: Q2.1 (B), R21.2
unnamed: C2.2, U1.2 (AVDD10OUT)
unnamed: R10.2, U1.26 (CRS/CRS_DV)
unnamed: C5.2, U1.29 (DVDD10OUT)
unnamed: R12.1, R17.1, U1.22 (MDC)
unnamed: R13.1, R18.1, U1.23 (MDIO)
unnamed: R15.2, U1.1 (RSET)
unnamed: R19.1, U1.8 (RXDV)
unnamed: R8.2, U1.9 (RXD[0])
unnamed: R1.2, R9.2, U1.10 (RXD[1])
unnamed: R5.2, U1.16 (TXD[0])
unnamed: R6.2, U1.17 (TXD[1])
unnamed: R7.2, U1.20 (TXEN)
unnamed: C3.1, R2.2, U1.21 (~PHYRSTB)
unnamed: C19.1, L2.1, U3.2 (VO)
unnamed: R31.2, R32.1, R33.2, U5.8 (VBUS)
